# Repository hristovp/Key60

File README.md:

I made a custom 60%(61 keys) keyboard with custom made PCB using (ATmega32u4) which is completely customizable.
I am adding evething needed for the project. It just take time to check if everythins works. :D

<kbd></kbd> <kbd></kbd>
<kbd></kbd> <kbd></kbd>

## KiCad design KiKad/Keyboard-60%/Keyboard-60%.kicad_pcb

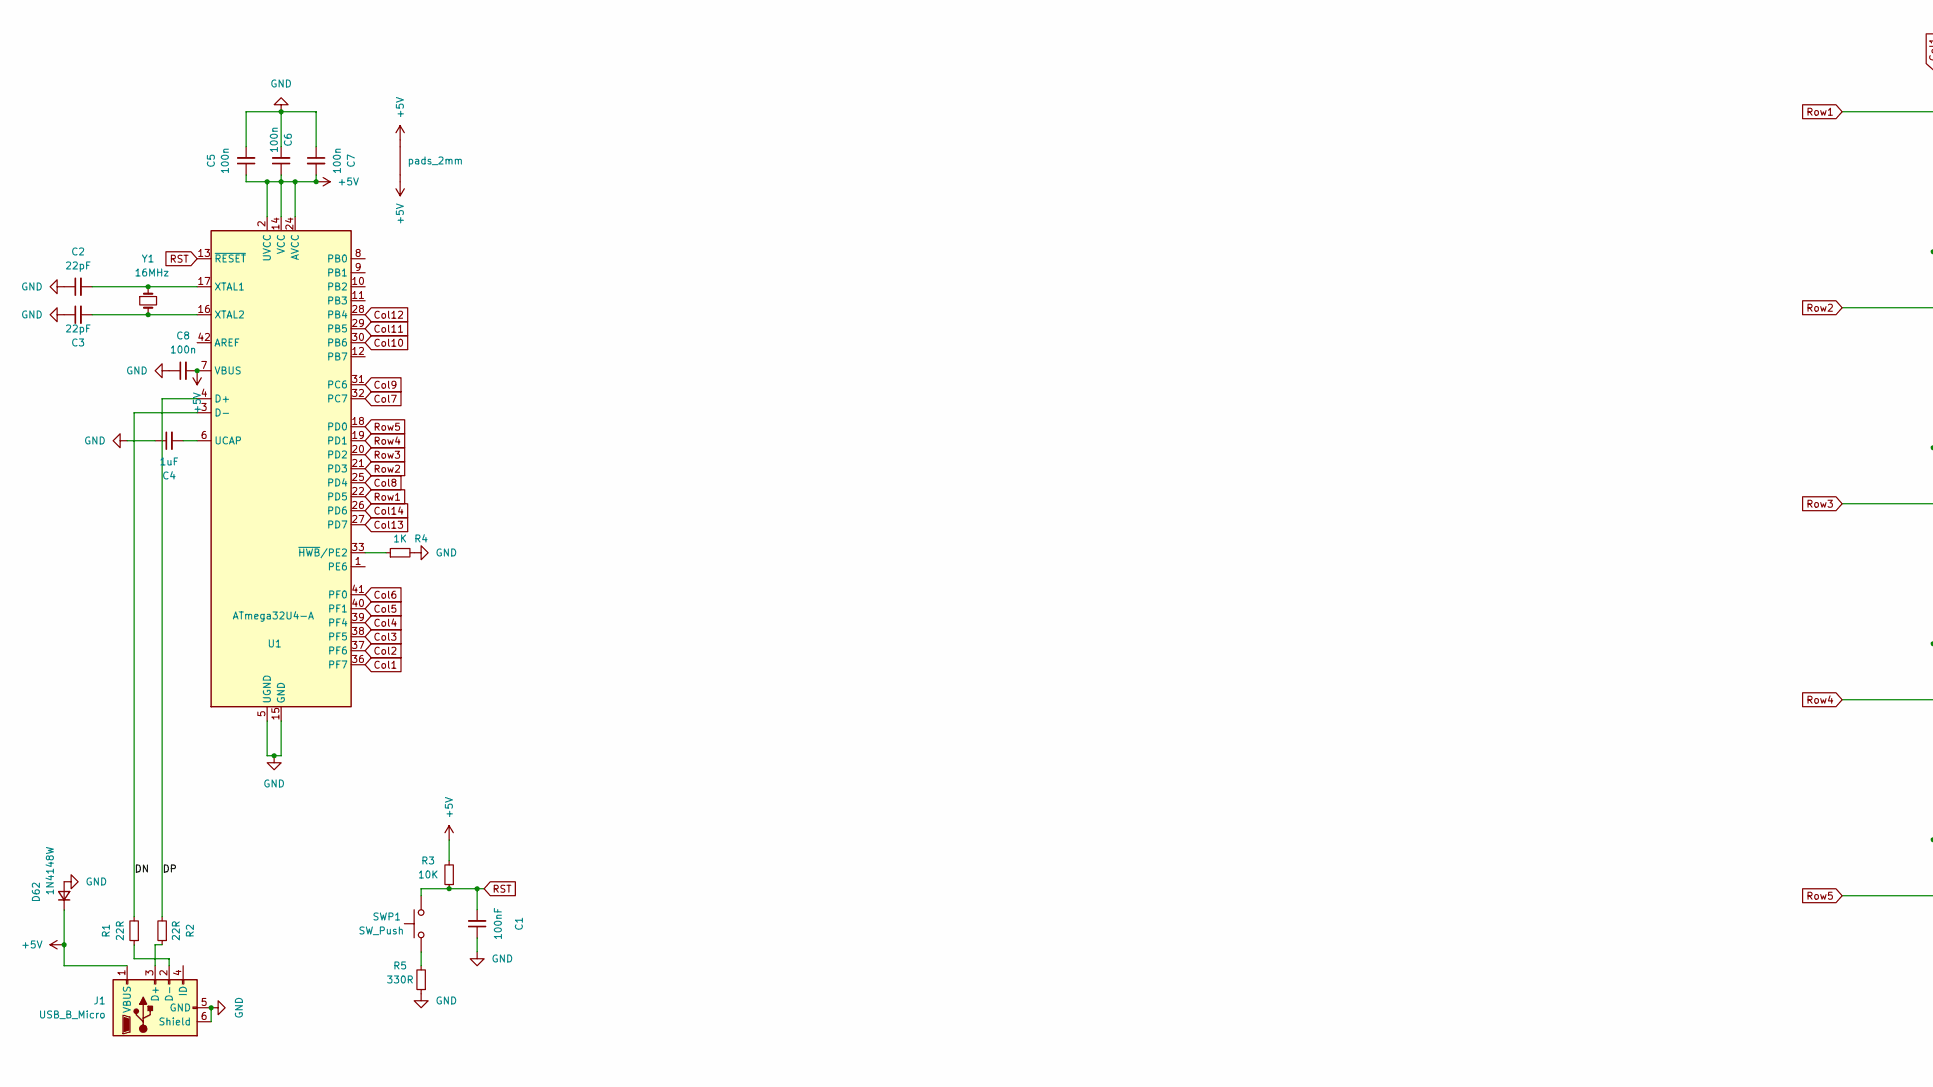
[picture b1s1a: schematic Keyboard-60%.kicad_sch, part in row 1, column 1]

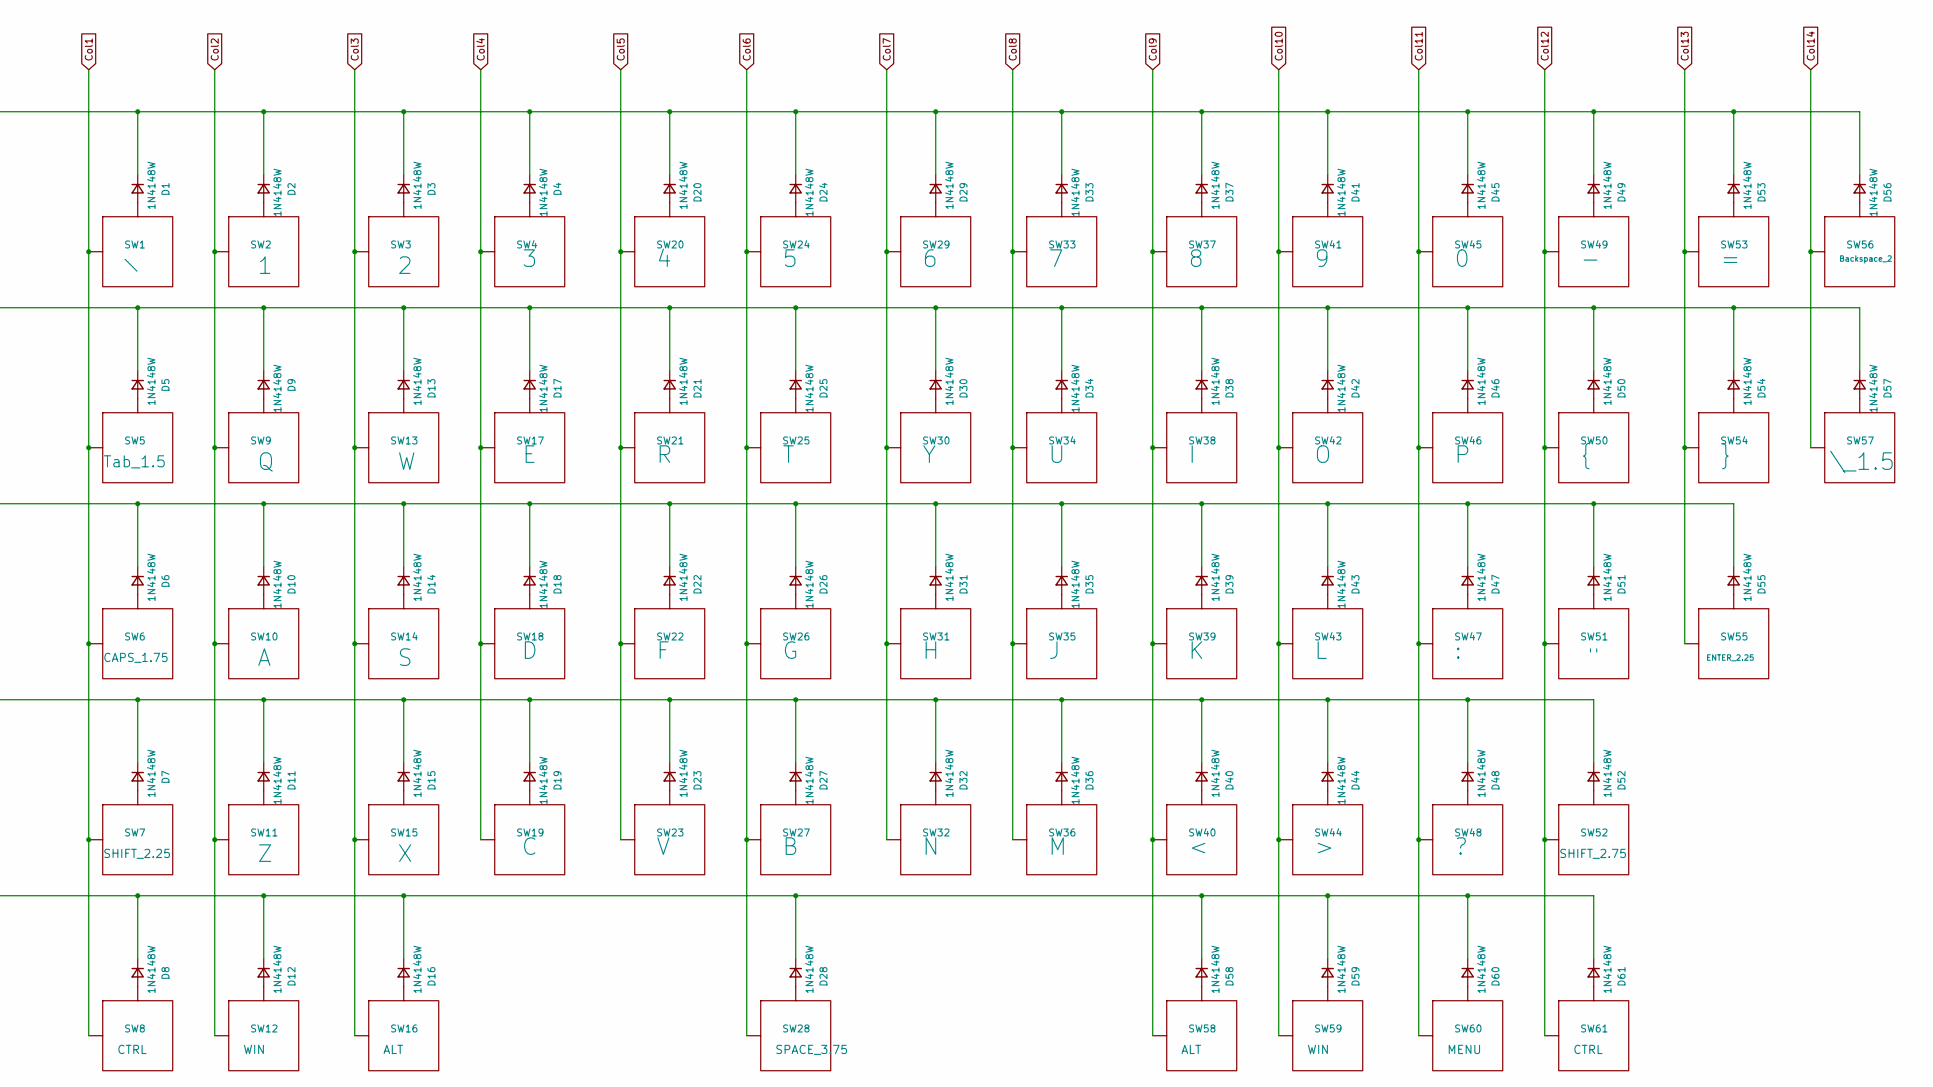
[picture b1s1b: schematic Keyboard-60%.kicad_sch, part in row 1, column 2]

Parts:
C1: 100nF; C_0805_2012Metric_Pad1.18x1.45mm_HandSolder
C2, C3: 22pF; C_0805_2012Metric_Pad1.18x1.45mm_HandSolder
C4: 1uF; C_0805_2012Metric_Pad1.18x1.45mm_HandSolder
C5, C6, C7, C8: 100n; C_0805_2012Metric_Pad1.18x1.45mm_HandSolder
D1, D2, D3, D4, D5, D6, D7, D8, D9, D10, D11, D12, D13, D14, D15, D16, D17, D18, D19, D20, D21, D22, D23, D24, D25, D26, D27, D28, D29, D30, D31, D32, D33, D34, D35, D36, D37, D38, D39, D40, D41, D42, D43, D44, D45, D46, D47, D48, D49, D50, D51, D52, D53, D54, D55, D56, D57, D58, D59, D60, D61, D62: 1N4148W; D_SOD-123
J1: USB_B_Micro; USB_Micro-B_Wuerth_629105150521_CircularHoles
R1, R2: 22R; R_1206_3216Metric_Pad1.30x1.75mm_HandSolder
R3: 10K; R_1206_3216Metric_Pad1.30x1.75mm_HandSolder
R4: 1K; R_1206_3216Metric_Pad1.30x1.75mm_HandSolder
R5: 330R; R_1206_3216Metric_Pad1.30x1.75mm_HandSolder
SW1: `; MX100
SW2: 1; MX100
SW3: 2; MX100
SW4: 3; MX100
SW5: Tab_1.5; MX150
SW6: CAPS_1.75; MX175
SW7: SHIFT_2.25; MX225
SW8, SW61: CTRL; MX125
SW9: Q; MX100
SW10: A; MX100
SW11: Z; MX100
SW12, SW59: WIN; MX125
SW13: W; MX100
SW14: S; MX100
SW15: X; MX100
SW16, SW58: ALT; MX125
SW17: E; MX100
SW18: D; MX100
SW19: C; MX100
SW20: 4; MX100
SW21: R; MX100
SW22: F; MX100
SW23: V; MX100
SW24: 5; MX100
SW25: T; MX100
SW26: G; MX100
SW27: B; MX100
SW28: SPACE_3.75; MX625
SW29: 6; MX100
SW30: Y; MX100
SW31: H; MX100
SW32: N; MX100
SW33: 7; MX100
SW34: U; MX100
SW35: J; MX100
SW36: M; MX100
SW37: 8; MX100
SW38: I; MX100
SW39: K; MX100
SW40: <; MX100
SW41: 9; MX100
SW42: O; MX100
SW43: L; MX100
SW44: >; MX100
SW45: 0; MX100
SW46: P; MX100
SW47: :; MX100
SW48: ?; MX100
SW49: -; MX100
SW50: {; MX100
SW51: "; MX100
SW52: SHIFT_2.75; MX275
SW53: =; MX100
SW54: }; MX100
SW55: ENTER_2.25; MX225
SW56: Backspace_2; MX200
SW57: \_1.5; MX150
SW60: MENU; MX125
SWP1: SW_Push; K2-1187SQ-A4SW-06
U1: ATmega32U4-A; ATmega32U4
Y1: 16MHz; Crystal_SMD_5032-2Pin_5.0x3.2mm_HandSoldering
p1: pads_2mm; pad-2mm

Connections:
+5V: C5.1, C6.1, C7.2, C8.2, D62.1 (K), J1.1 (VBUS), R3.2, U1.2 (UVCC), U1.7 (VBUS), U1.14 (VCC), U1.24 (AVCC), U1.34 (VCC), U1.44 (AVCC), p1.1, p1.2
/DN: R1.2, U1.3 (D-)
/DP: R2.2, U1.4 (D+)
Col1: SW1.1 (Col), SW5.1 (Col), SW6.1 (Col), SW7.1 (Col), SW8.1 (Col), U1.36 (PF7)
Col2: SW2.1 (Col), SW9.1 (Col), SW10.1 (Col), SW11.1 (Col), SW12.1 (Col), U1.37 (PF6)
Col3: SW3.1 (Col), SW13.1 (Col), SW14.1 (Col), SW15.1 (Col), SW16.1 (Col), U1.38 (PF5)
Col4: SW4.1 (Col), SW17.1 (Col), SW18.1 (Col), SW19.1 (Col), U1.39 (PF4)
Col5: SW20.1 (Col), SW21.1 (Col), SW22.1 (Col), SW23.1 (Col), U1.40 (PF1)
Col6: SW24.1 (Col), SW25.1 (Col), SW26.1 (Col), SW27.1 (Col), SW28.1 (Col), U1.41 (PF0)
Col7: SW29.1 (Col), SW30.1 (Col), SW31.1 (Col), SW32.1 (Col), U1.32 (PC7)
Col8: SW33.1 (Col), SW34.1 (Col), SW35.1 (Col), SW36.1 (Col), U1.25 (PD4)
Col9: SW37.1 (Col), SW38.1 (Col), SW39.1 (Col), SW40.1 (Col), SW58.1 (Col), U1.31 (PC6)
Col10: SW41.1 (Col), SW42.1 (Col), SW43.1 (Col), SW44.1 (Col), SW59.1 (Col), U1.30 (PB6)
Col11: SW45.1 (Col), SW46.1 (Col), SW47.1 (Col), SW48.1 (Col), SW60.1 (Col), U1.29 (PB5)
Col12: SW49.1 (Col), SW50.1 (Col), SW51.1 (Col), SW52.1 (Col), SW61.1 (Col), U1.28 (PB4)
Col13: SW53.1 (Col), SW54.1 (Col), SW55.1 (Col), U1.27 (PD7)
Col14: SW56.1 (Col), SW57.1 (Col), U1.26 (PD6)
GND: C1.1, C2.1, C3.1, C4.1, C5.2, C6.2, C7.1, C8.1, D62.2 (A), J1.5 (GND), J1.6 (Shield), R4.2, R5.1, U1.5 (UGND), U1.15 (GND), U1.23 (GND), U1.35 (GND), U1.43 (GND)
unnamed: C2.2, U1.17 (XTAL1), Y1.1
unnamed: C3.2, U1.16 (XTAL2), Y1.2
unnamed: C4.2, U1.6 (UCAP)
unnamed: D1.2 (A), SW1.2 (Row)
unnamed: D2.2 (A), SW2.2 (Row)
unnamed: D3.2 (A), SW3.2 (Row)
unnamed: D4.2 (A), SW4.2 (Row)
unnamed: D5.2 (A), SW5.2 (Row)
unnamed: D6.2 (A), SW6.2 (Row)
unnamed: D7.2 (A), SW7.2 (Row)
unnamed: D8.2 (A), SW8.2 (Row)
unnamed: D9.2 (A), SW9.2 (Row)
unnamed: D10.2 (A), SW10.2 (Row)
unnamed: D11.2 (A), SW11.2 (Row)
unnamed: D12.2 (A), SW12.2 (Row)
unnamed: D13.2 (A), SW13.2 (Row)
unnamed: D14.2 (A), SW14.2 (Row)
unnamed: D15.2 (A), SW15.2 (Row)
unnamed: D16.2 (A), SW16.2 (Row)
unnamed: D17.2 (A), SW17.2 (Row)
unnamed: D18.2 (A), SW18.2 (Row)
unnamed: D19.2 (A), SW19.2 (Row)
unnamed: D20.2 (A), SW20.2 (Row)
unnamed: D21.2 (A), SW21.2 (Row)
unnamed: D22.2 (A), SW22.2 (Row)
unnamed: D23.2 (A), SW23.2 (Row)
unnamed: D24.2 (A), SW24.2 (Row)
unnamed: D25.2 (A), SW25.2 (Row)
unnamed: D26.2 (A), SW26.2 (Row)
unnamed: D27.2 (A), SW27.2 (Row)
unnamed: D28.2 (A), SW28.2 (Row)
unnamed: D29.2 (A), SW29.2 (Row)
unnamed: D30.2 (A), SW30.2 (Row)
unnamed: D31.2 (A), SW31.2 (Row)
unnamed: D32.2 (A), SW32.2 (Row)
unnamed: D33.2 (A), SW33.2 (Row)
unnamed: D34.2 (A), SW34.2 (Row)
unnamed: D35.2 (A), SW35.2 (Row)
unnamed: D36.2 (A), SW36.2 (Row)
unnamed: D37.2 (A), SW37.2 (Row)
unnamed: D38.2 (A), SW38.2 (Row)
unnamed: D39.2 (A), SW39.2 (Row)
unnamed: D40.2 (A), SW40.2 (Row)
unnamed: D41.2 (A), SW41.2 (Row)
unnamed: D42.2 (A), SW42.2 (Row)
unnamed: D43.2 (A), SW43.2 (Row)
unnamed: D44.2 (A), SW44.2 (Row)
unnamed: D45.2 (A), SW45.2 (Row)
unnamed: D46.2 (A), SW46.2 (Row)
unnamed: D47.2 (A), SW47.2 (Row)
unnamed: D48.2 (A), SW48.2 (Row)
unnamed: D49.2 (A), SW49.2 (Row)
unnamed: D50.2 (A), SW50.2 (Row)
unnamed: D51.2 (A), SW51.2 (Row)
unnamed: D52.2 (A), SW52.2 (Row)
unnamed: D53.2 (A), SW53.2 (Row)
unnamed: D54.2 (A), SW54.2 (Row)
unnamed: D55.2 (A), SW55.2 (Row)
unnamed: D56.2 (A), SW56.2 (Row)
unnamed: D57.2 (A), SW57.2 (Row)
unnamed: D58.2 (A), SW58.2 (Row)
unnamed: D59.2 (A), SW59.2 (Row)
unnamed: D60.2 (A), SW60.2 (Row)
unnamed: D61.2 (A), SW61.2 (Row)
unnamed: J1.2 (D-), R1.1
unnamed: J1.3 (D+), R2.1
unnamed: R4.1, U1.33 (~HWB/PE2)
unnamed: R5.2, SWP1.1
RST: C1.2, R3.1, SWP1.2, U1.13 (~RESET)
Row1: D1.1 (K), D2.1 (K), D3.1 (K), D4.1 (K), D20.1 (K), D24.1 (K), D29.1 (K), D33.1 (K), D37.1 (K), D41.1 (K), D45.1 (K), D49.1 (K), D53.1 (K), D56.1 (K), U1.22 (PD5)
Row2: D5.1 (K), D9.1 (K), D13.1 (K), D17.1 (K), D21.1 (K), D25.1 (K), D30.1 (K), D34.1 (K), D38.1 (K), D42.1 (K), D46.1 (K), D50.1 (K), D54.1 (K), D57.1 (K), U1.21 (PD3)
Row3: D6.1 (K), D10.1 (K), D14.1 (K), D18.1 (K), D22.1 (K), D26.1 (K), D31.1 (K), D35.1 (K), D39.1 (K), D43.1 (K), D47.1 (K), D51.1 (K), D55.1 (K), U1.20 (PD2)
Row4: D7.1 (K), D11.1 (K), D15.1 (K), D19.1 (K), D23.1 (K), D27.1 (K), D32.1 (K), D36.1 (K), D40.1 (K), D44.1 (K), D48.1 (K), D52.1 (K), U1.19 (PD1)
Row5: D8.1 (K), D12.1 (K), D16.1 (K), D28.1 (K), D58.1 (K), D59.1 (K), D60.1 (K), D61.1 (K), U1.18 (PD0)

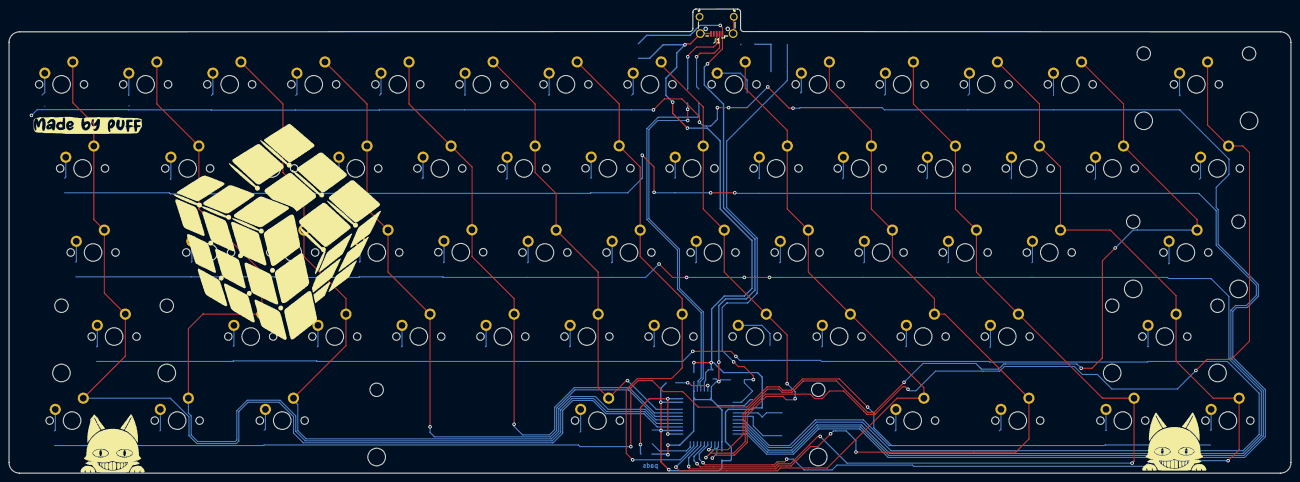
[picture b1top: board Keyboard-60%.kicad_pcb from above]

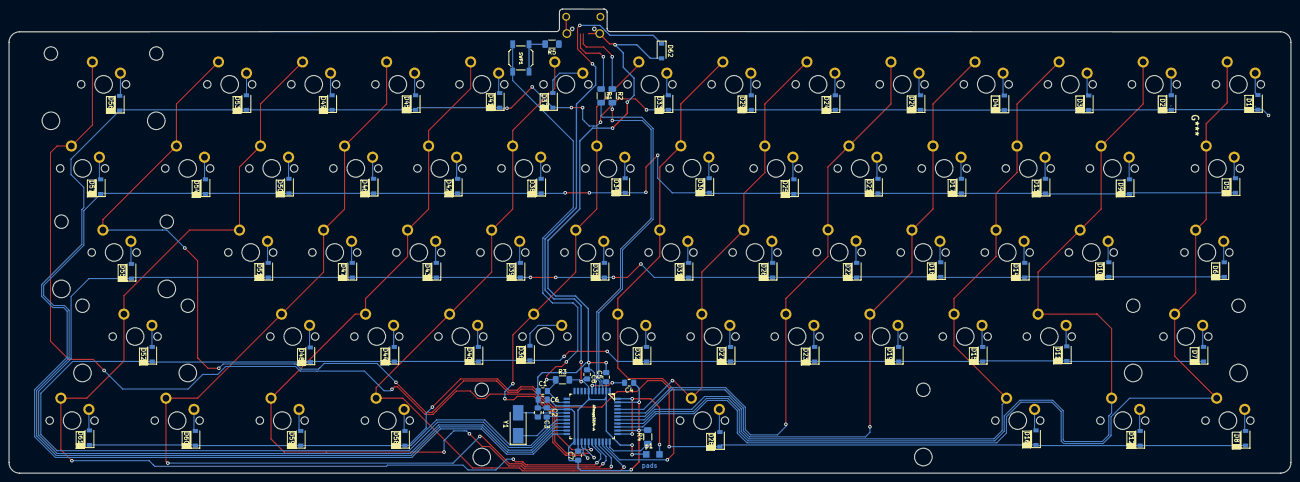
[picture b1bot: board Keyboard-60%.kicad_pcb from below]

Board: 2 copper layers, 290.5 x 105.2 mm, 141 parts (140 on the bottom side), 92 nets.

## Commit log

2022-08-21 Files and schematics
2022-08-21 Add pictures
2022-08-21 PCB picture
2022-08-21 Components
2022-08-21 PCB(PIC)
2022-08-27 pic update
